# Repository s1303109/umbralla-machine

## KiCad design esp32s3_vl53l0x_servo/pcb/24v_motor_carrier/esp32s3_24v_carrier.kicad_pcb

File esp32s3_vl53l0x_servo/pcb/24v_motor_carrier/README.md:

# ESP32-S3／24V 馬達載板：KiCad 實作草稿

**狀態：DRAFT_NOT_FOR_FABRICATION。已實際建立原理圖、元件擺放、雙層銅箔、過孔與背面 GND 填充；未取得實物封裝與電氣驗證前，不可直接送製板。**

開啟 `esp32s3_24v_carrier.kicad_pro`。本專案附有本地符號庫、封裝庫及兩個 lib-table，不需要安裝全域元件庫。沒有操作遠端電腦上的 KiCad 視窗，也沒有修改原韌體或舊接線圖。

## 已完成

- 真正的 KiCad 8 `.kicad_sch`、`.kicad_pcb`、`.kicad_pro`，不是只有圖片。
- 23個封裝（含3個暫定固定孔）、33個功能網路；未使用 GPIO 另保留 KiCad 的單焊盤 NC 網路。
- 板外框包圍尺寸 **91.44 × 76.20 mm**，天線側有退讓切口；這是可檢查的第一版草稿，不宣稱最小尺寸或孔位已核准。
- 22個使用中的 GPIO 對照現有 `main/main.c` 與 `main/lcd_display.c`，GPIO1留空、GPIO35／36／37保留不接。
- R3 為 +5V_IN 到 K2_IN_L 的上拉；Q2 C 直接接 K2_IN_L。
- HC ECHO → R4 10kΩ → GPIO6分壓中點 → R5 20kΩ → GND。
- D1 有環端 K 接馬達切換正極、A 接GND；位於 K2 NO 後，與馬達並聯。
- 24V／馬達切換正極及直接回電源的馬達回流，用 **2.032mm** 預設銅線寬。此數字不構成任意銅厚、溫升、啟動電流下的容量保證。
- KiCad 8.0.9 原生 ERC／DRC、PCB與原理圖一致性檢查及網表逐端點比對。最後結果見 [reports/validation.json](reports/validation.json)。

## 如何看圖

- [原理圖 PDF](preview/schematic.pdf)
- [原理圖 PNG](preview/schematic.png)
- [完整雙層 PCB 預覽](preview/board_layers.png)
- [實際元件擺放與極性標示](preview/placement.png)
- [前面銅箔與絲印](preview/front.png)
- [背面銅箔](preview/back.png)
- [接頭腳位表 CSV](connector_pinout.csv)
- [全元件網路表 CSV](wiring_matrix.csv)
- [BOM／封裝狀態 CSV](bom.csv)

PCB上的 A1 是 ESP32 開發板插座。左側保留 USB 插拔方向，右側為天線退讓區；LCD以外接接頭J2表示，沒有將未確認的整片LCD孔位當成已核准製造尺寸。U5／U11等照片中的參考代號沒有直接沿用為本專案的實物焊盤代號。

擺放預覽依實際PCB封裝與焊盤座標重繪清楚標籤；原生F.Fab輸出另保留在 `preview/placement_native.svg`。銅箔與原理圖預覽均由KiCad原生輸出。

## 接頭與跳帽

**所有外接排針順序都是這份新載板定義的順序，不是宣稱與原LCD／模組原生排針完全相同。必須依下表和實物端子名稱製作接線，不能盲插。** 第1腳以方形焊盤標示。

| 元件 | 腳位順序 |
|---|---|
| J1 DC輸入，暫定5.08mm | 1＝外部+5V、2＝COM/GND、3＝+24V |
| JP1 外部5V連接 | 1＝+5V_IN、2＝+5V_ESP；使用外部5V時連接，USB供電前依原方案移除，不宣稱自動切換 |
| J2 LCD，1×16／2.54mm | 1 GND、2 +5V_ESP、3 RST、4 CS、5 RS、6 WR、7 RD、8 D0、9 D1、10 D2、11 D3、12 D4、13 D5、14 D6、15 D7、16 NC |
| J3 ToF1 | 1 VIN、2 GND、3 SCL、4 SDA、5 GPIO1/INT未接、6 XSHUT |
| J4 ToF2 | 1 VIN、2 GND、3 SCL、4 SDA |
| JP2／JP3 ToF供電 | 1 3V3、2 VIN、3 +5V_ESP；**預設不裝跳帽**，先確認模組VIN及I2C上拉電壓 |
| J5 HC-SR04 | 1 VCC、2 TRIG、3 ECHO、4 GND；ECHO經板上分壓後才到GPIO6 |
| J6 K1控制 | 1 DC+／+5V_IN、2 DC−／GND、3 IN／GPIO7；模組設H觸發 |
| J7 K2控制 | 1 VCC／+5V_ESP、2 GND、3 IN／K2_IN_L；由Q2拉低啟動 |
| J8 K2直流接點，暫定5.08mm | 1 → K2 COM（+24V）；2 ← K2 NO（切換正極）；NC不接 |
| J9 馬達，暫定5.08mm | 1 馬達＋、2 馬達－ |

J6只接K1控制側。**110V、L／N／PE與K1市電接點全部留在載板外**；本PCB沒有這些網路。

Q2封裝以 **E、B、C** 功能字母編號，使用暫定2.54mm引線成形／插接排列；它不是已確認的S9014、CS9013或2N3904通用腳序。E／B／C與D1 K／A已加在絲印，裝配前仍須核對實際零件。

## 製板前仍須完成

1. 實際 YD-ESP32-S3 V1.5 每腳、排距、排母、孔徑、USB與天線／機殼淨空確認。
2. 全部接頭的實際料號、腳距、線序、額定電流與線徑；LCD本體與排線接法。
3. ToF1／ToF2 供電與I2C上拉。JP2／JP3目前是開路選擇，未裝跳帽時感測器不會上電。
4. Q2實物型號、廠牌、腳序與封裝；K1輸入相容性、K2 IN電流與觸發門檻。
5. 24V電源啟動能力、馬達實際電流、K2直流馬達接點能力及D1續流／熱條件。
6. 銅厚、導線與端子的電流容量、過流保護、實際模組高度／固定孔及機構。

原D-50B照片為24V／1A，不能因布線完成就認定能啟動表列堵轉3A的馬達。程式仍含伺服測試服務；本PCB將GPIO1留空，未更動控制程式。

## 重產生與檢查

一般使用只需在 KiCad 8 或更新版本開啟 `.kicad_pro`。下列指令用於重建；需要KiCad 8的pcbnew Python綁定及CLI：

```sh
python3 scripts/build_project.py
python3 scripts/route_project.py
python3 scripts/finish_project.py
kicad-cli sch erc --format json --exit-code-violations -o reports/erc.json esp32s3_24v_carrier.kicad_sch
kicad-cli sch export netlist --format kicadxml -o reports/netlist.xml esp32s3_24v_carrier.kicad_sch
kicad-cli pcb drc --format json --schematic-parity --exit-code-violations -o reports/drc.json esp32s3_24v_carrier.kicad_pcb
python3 scripts/check_project.py
```

`build_project.py`會重新產生未完整布線的起始PCB；若要保留手動編輯，先另存副本再執行。腳本不讀寫韌體。

本機工具位於 `/opt/kicad8-validation`；環境設定已收在 `scripts/run_local.sh`。專案本身不依賴該絕對路徑即可在KiCad開啟。最初的檢查報告留在 `reports/history/`，正式結果以 `reports/erc.json`、`reports/drc.json`、`reports/validation.json`為準。

## 參考

- [Espressif：模組在載板上的天線擺放](https://docs.espressif.com/projects/esp-hardware-design-guidelines/en/latest/esp32s3/pcb-layout-design.html#general-principles-of-pcb-layout-for-modules-positioning-a-module-on-a-base-board)
- [Vishay 1N5408資料表](https://www.vishay.com/docs/88516/1n5400.pdf)：額定有熱條件，不能只看3A字樣。
- 本地原始庫來源、44腳對照、GPIO檔案SHA-256與待確認項目保留在 `design_contract.json`、`contract_review.md`。

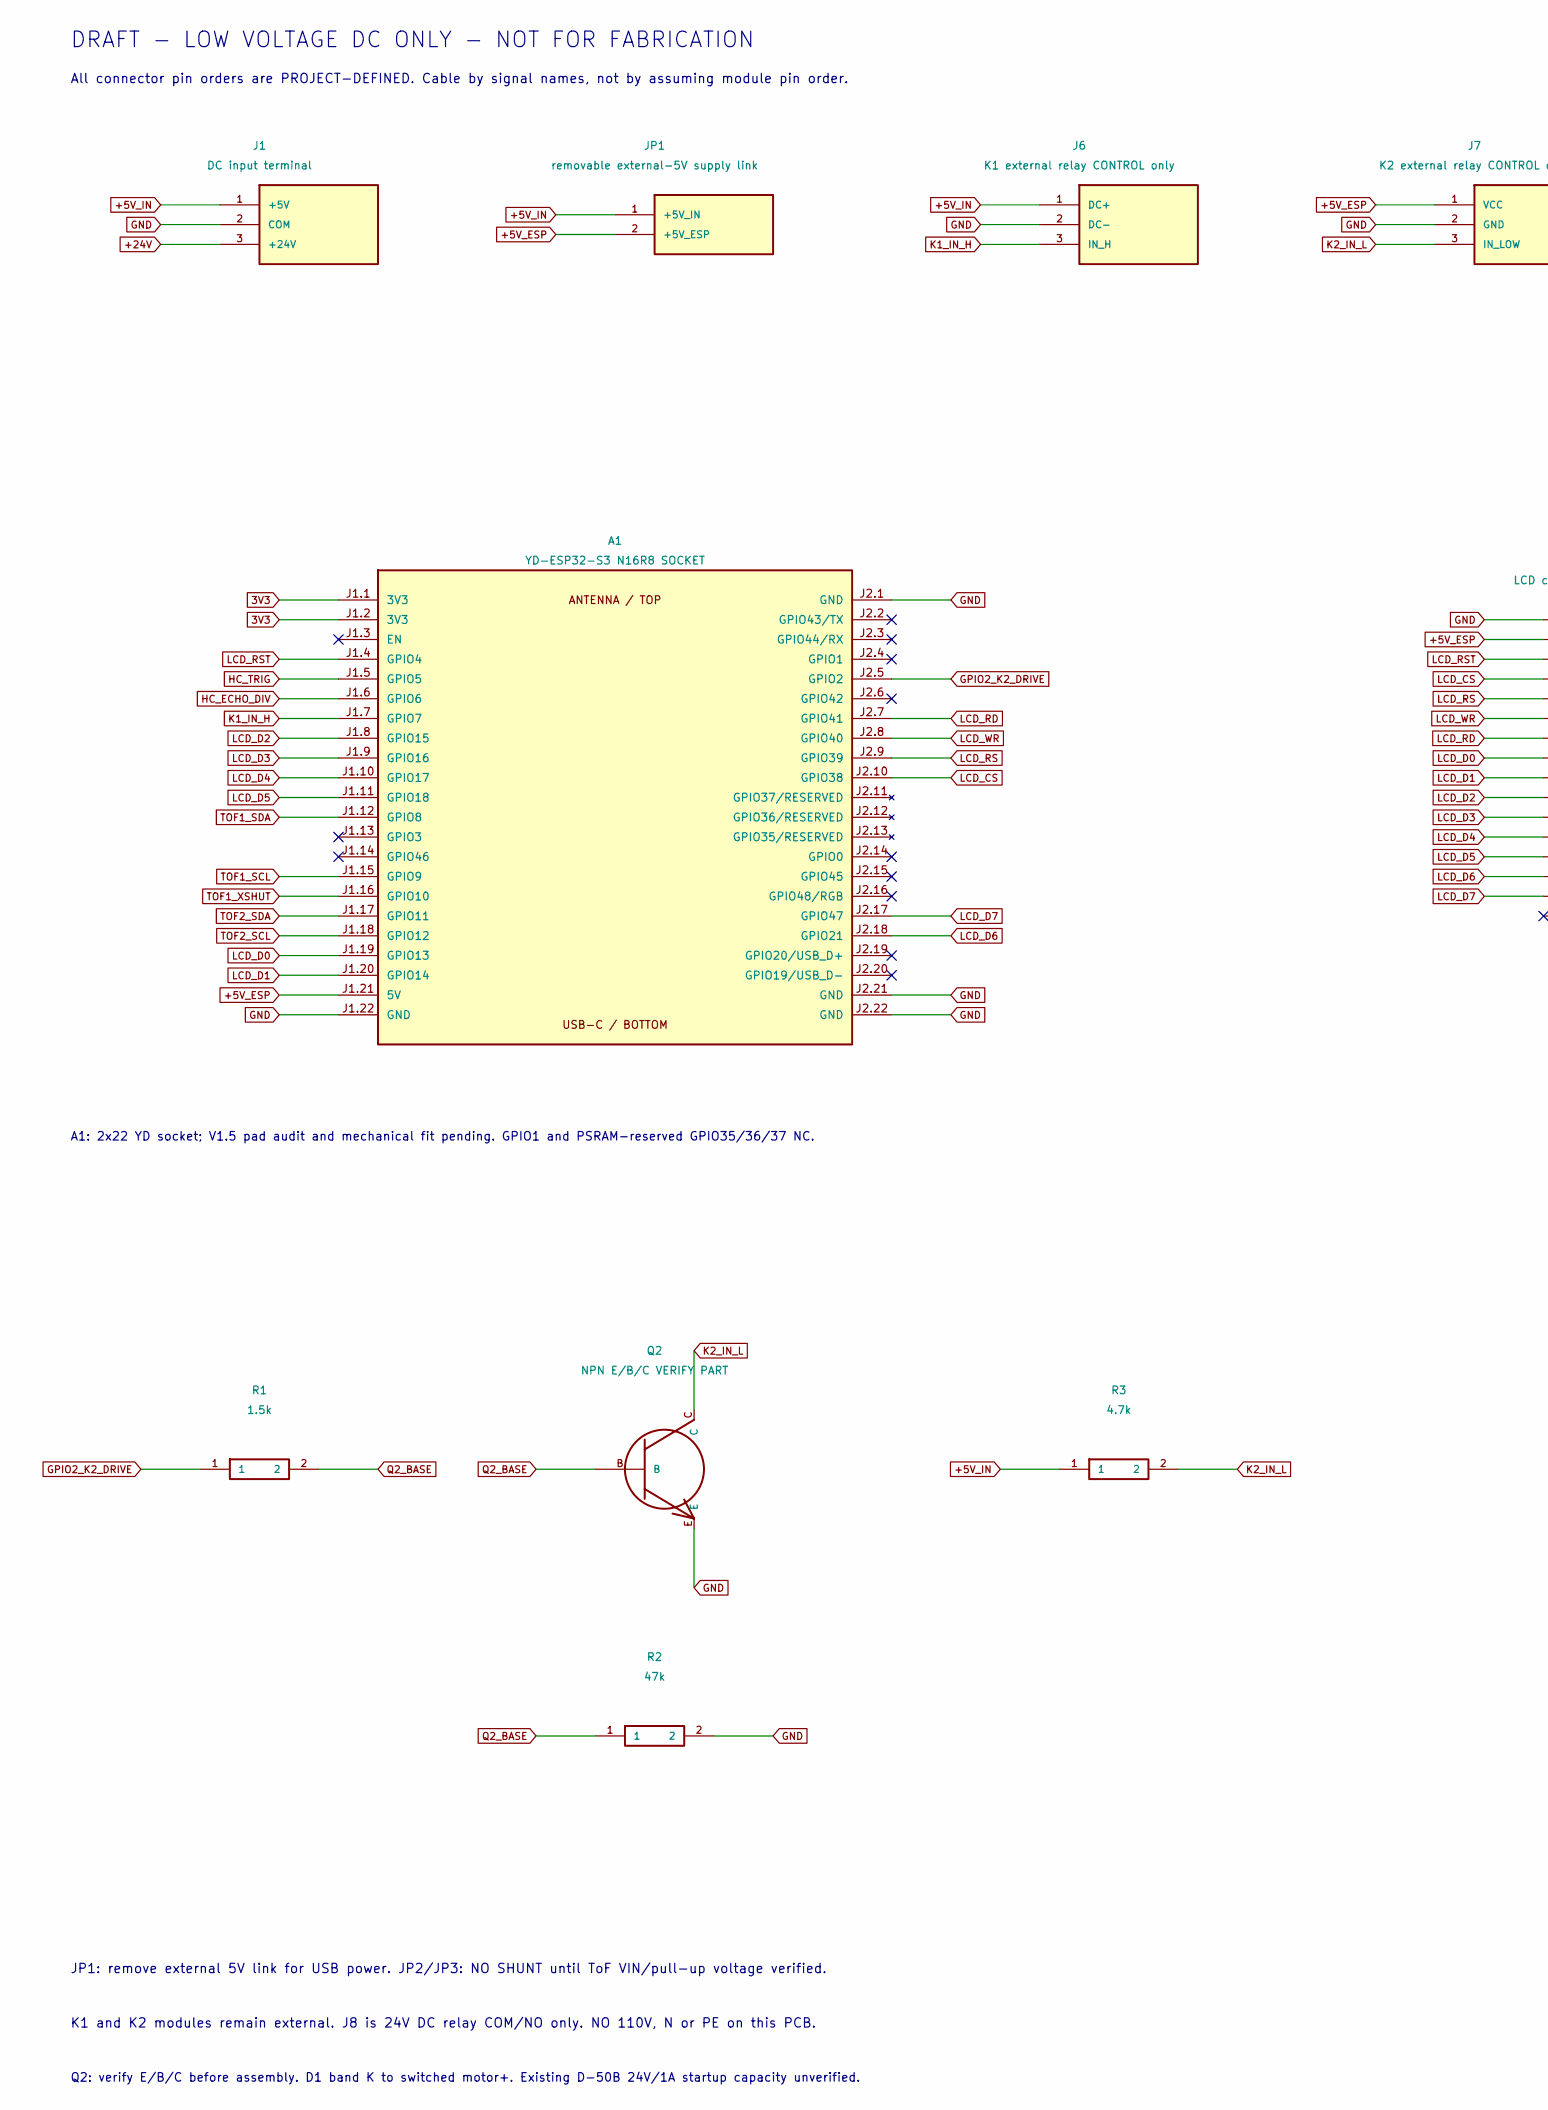
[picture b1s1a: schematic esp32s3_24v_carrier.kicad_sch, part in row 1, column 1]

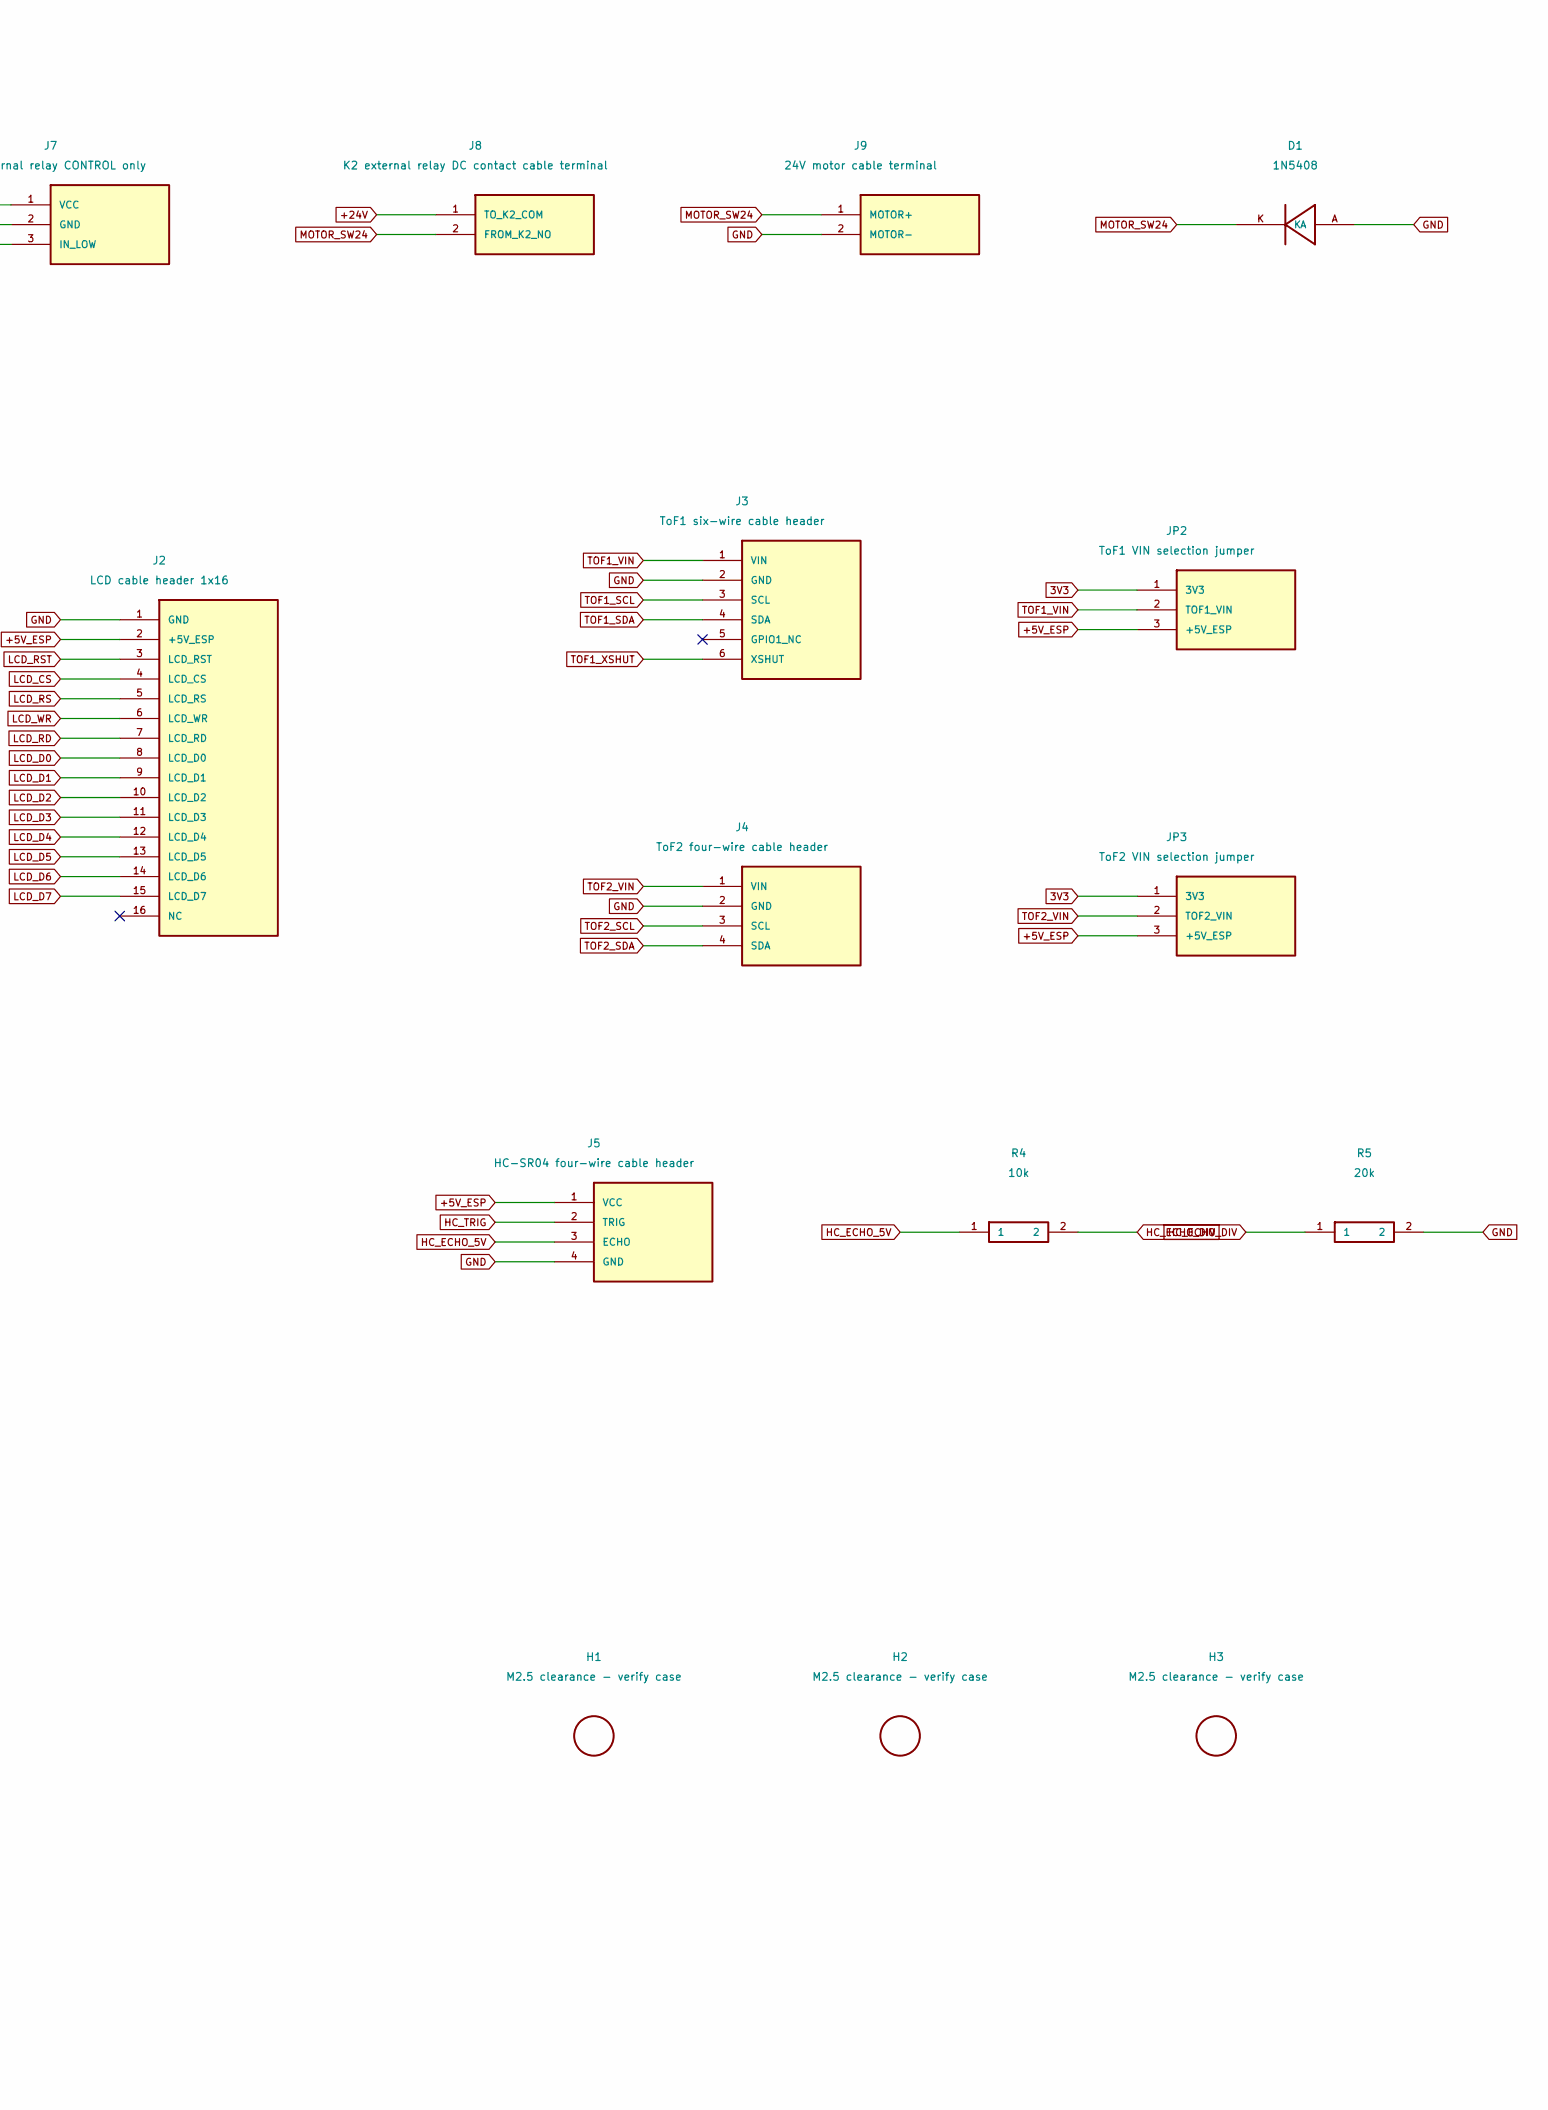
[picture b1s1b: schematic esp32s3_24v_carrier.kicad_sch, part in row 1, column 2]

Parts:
A1: YD-ESP32-S3 N16R8 SOCKET; YD-ESP32-S3_2x22_P2.54mm_Row25.40mm
D1: 1N5408; D_DO201_P15.24
H1, H2, H3: M2.5 clearance - verify case; MountingHole_2.7_GENERIC
J1: DC input terminal; Terminal_1x3_P5.08_GENERIC
J2: LCD cable header 1x16; Header_1x16_P2.54
J3: ToF1 six-wire cable header; Header_1x6_P2.54
J4: ToF2 four-wire cable header; Header_1x4_P2.54
J5: HC-SR04 four-wire cable header; Header_1x4_P2.54
J6: K1 external relay CONTROL only; Header_1x3_P2.54
J7: K2 external relay CONTROL only; Header_1x3_P2.54
J8: K2 external relay DC contact cable terminal; Terminal_1x2_P5.08_GENERIC
J9: 24V motor cable terminal; Terminal_1x2_P5.08_GENERIC
JP1: removable external-5V supply link; Header_1x2_P2.54
JP2: ToF1 VIN selection jumper; Header_1x3_P2.54
JP3: ToF2 VIN selection jumper; Header_1x3_P2.54
Q2: NPN E/B/C VERIFY PART; NPN_EBC_Wire_Form_VERIFY
R1: 1.5k; R_Axial_P7.62
R2: 47k; R_Axial_P7.62
R3: 4.7k; R_Axial_P7.62
R4: 10k; R_Axial_P7.62
R5: 20k; R_Axial_P7.62

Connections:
3V3: A1.J1.1 (3V3), A1.J1.2 (3V3), JP2.1 (3V3), JP3.1 (3V3)
+5V_ESP: A1.J1.21 (5V), J2.2 (+5V_ESP), J5.1 (VCC), J7.1 (VCC), JP1.2 (+5V_ESP), JP2.3 (+5V_ESP), JP3.3 (+5V_ESP)
+5V_IN: J1.1 (+5V), J6.1 (DC+), JP1.1 (+5V_IN), R3.1
+24V: J1.3 (+24V), J8.1 (TO_K2_COM)
GND: A1.J1.22 (GND), A1.J2.1 (GND), A1.J2.21 (GND), A1.J2.22 (GND), D1.A, J1.2 (COM), J2.1 (GND), J3.2 (GND), J4.2 (GND), J5.4 (GND), J6.2 (DC-), J7.2 (GND), J9.2 (MOTOR-), Q2.E, R2.2, R5.2
GPIO2_K2_DRIVE: A1.J2.5 (GPIO2), R1.1
HC_ECHO_5V: J5.3 (ECHO), R4.1
HC_ECHO_DIV: A1.J1.6 (GPIO6), R4.2, R5.1
HC_TRIG: A1.J1.5 (GPIO5), J5.2 (TRIG)
K1_IN_H: A1.J1.7 (GPIO7), J6.3 (IN_H)
K2_IN_L: J7.3 (IN_LOW), Q2.C, R3.2
LCD_CS: A1.J2.10 (GPIO38), J2.4 (LCD_CS)
LCD_D0: A1.J1.19 (GPIO13), J2.8 (LCD_D0)
LCD_D1: A1.J1.20 (GPIO14), J2.9 (LCD_D1)
LCD_D2: A1.J1.8 (GPIO15), J2.10 (LCD_D2)
LCD_D3: A1.J1.9 (GPIO16), J2.11 (LCD_D3)
LCD_D4: A1.J1.10 (GPIO17), J2.12 (LCD_D4)
LCD_D5: A1.J1.11 (GPIO18), J2.13 (LCD_D5)
LCD_D6: A1.J2.18 (GPIO21), J2.14 (LCD_D6)
LCD_D7: A1.J2.17 (GPIO47), J2.15 (LCD_D7)
LCD_RD: A1.J2.7 (GPIO41), J2.7 (LCD_RD)
LCD_RS: A1.J2.9 (GPIO39), J2.5 (LCD_RS)
LCD_RST: A1.J1.4 (GPIO4), J2.3 (LCD_RST)
LCD_WR: A1.J2.8 (GPIO40), J2.6 (LCD_WR)
MOTOR_SW24: D1.K, J8.2 (FROM_K2_NO), J9.1 (MOTOR+)
Q2_BASE: Q2.B, R1.2, R2.1
TOF1_SCL: A1.J1.15 (GPIO9), J3.3 (SCL)
TOF1_SDA: A1.J1.12 (GPIO8), J3.4 (SDA)
TOF1_VIN: J3.1 (VIN), JP2.2 (TOF1_VIN)
TOF1_XSHUT: A1.J1.16 (GPIO10), J3.6 (XSHUT)
TOF2_SCL: A1.J1.18 (GPIO12), J4.3 (SCL)
TOF2_SDA: A1.J1.17 (GPIO11), J4.4 (SDA)
TOF2_VIN: J4.1 (VIN), JP3.2 (TOF2_VIN)

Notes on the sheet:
DRAFT - LOW VOLTAGE DC ONLY - NOT FOR FABRICATION
All connector pin orders are PROJECT-DEFINED. Cable by signal names, not by assuming module pin order.
A1: 2x22 YD socket; V1.5 pad audit and mechanical fit pending. GPIO1 and PSRAM-reserved GPIO35/36/37 NC.
JP1: remove external 5V link for USB power. JP2/JP3: NO SHUNT until ToF VIN/pull-up voltage verified.
K1 and K2 modules remain external. J8 is 24V DC relay COM/NO only. NO 110V, N or PE on this PCB.
Q2: verify E/B/C before assembly. D1 band K to switched motor+. Existing D-50B 24V/1A startup capacity unverified.

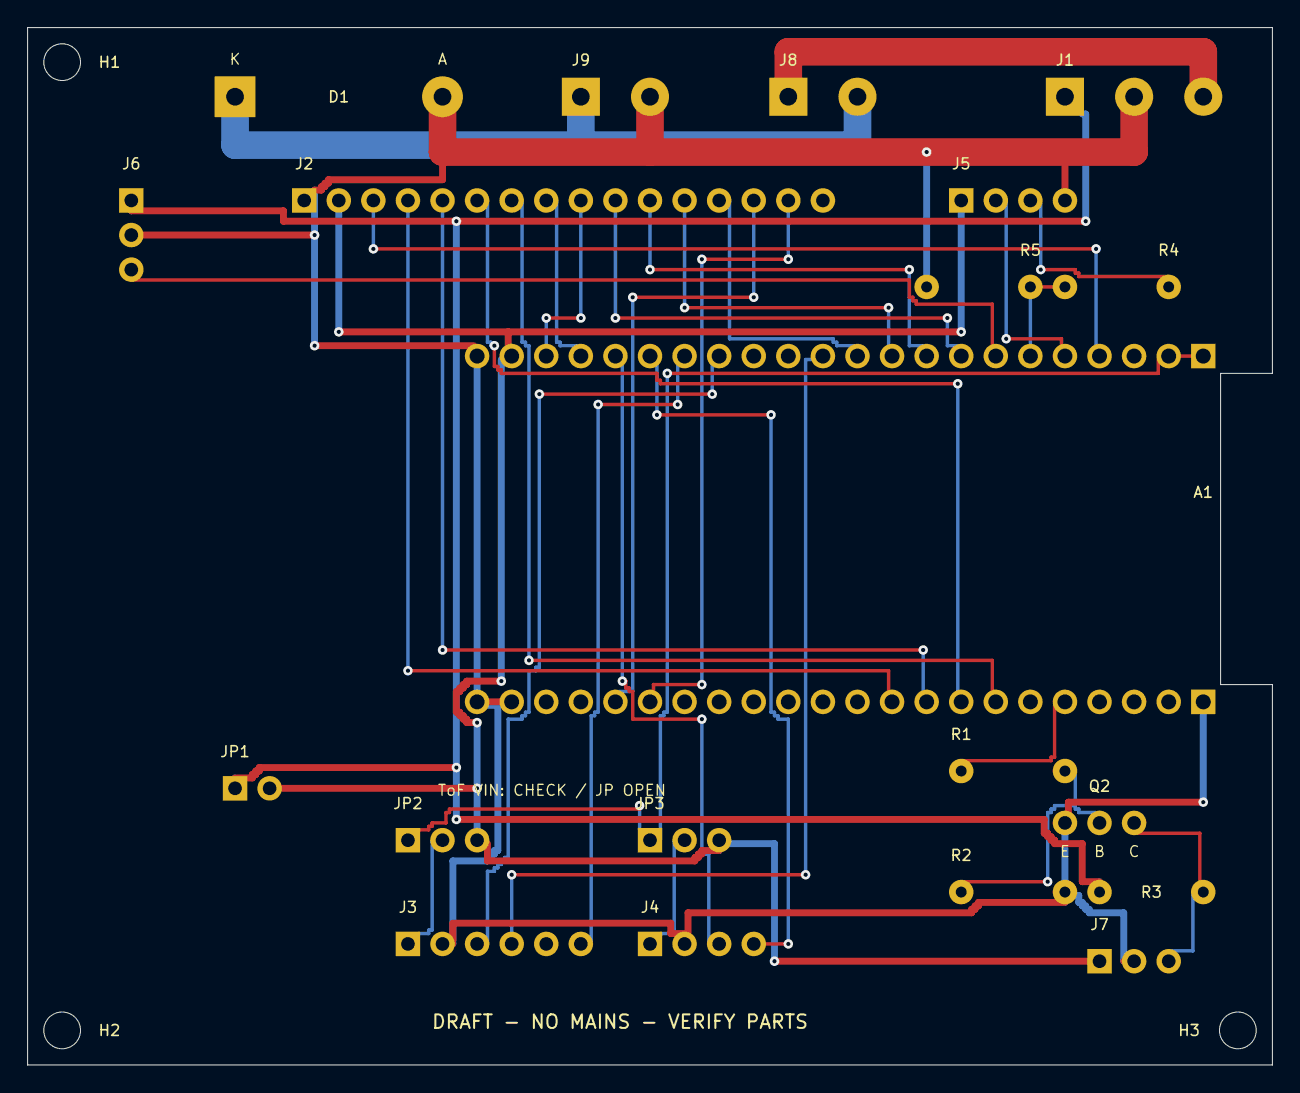
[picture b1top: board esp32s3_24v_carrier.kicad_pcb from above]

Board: 2 copper layers, 91.4 x 76.2 mm, 23 parts (0 on the bottom side), 33 nets.

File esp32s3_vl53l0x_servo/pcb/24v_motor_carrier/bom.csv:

Reference,Value,Kind,Footprint,Verification
A1,YD-ESP32-S3 N16R8 SOCKET,ESP32 development-board socket,CarrierDraft:YD-ESP32-S3_2x22_P2.54mm_Row25.40mm,V1.4 source mapping; V1.5 physical audit pending
J1,DC input terminal,DC input terminal,CarrierDraft:Terminal_1x3_P5.08_GENERIC,project-defined pin order; terminal model/current rating pending
JP1,removable external-5V supply link,removable external-5V supply link,CarrierDraft:Header_1x2_P2.54,remove before USB-powered operation; no automatic power ORing is claimed
J2,LCD cable header 1x16,LCD cable header 1x16,CarrierDraft:Header_1x16_P2.54,project-defined cable header; NOT native shield physical pin order; pin16 NC
J3,ToF1 six-wire cable header,ToF1 six-wire cable header,CarrierDraft:Header_1x6_P2.54,logical interface order only; actual connector/cable must be verified
J4,ToF2 four-wire cable header,ToF2 four-wire cable header,CarrierDraft:Header_1x4_P2.54,logical interface order only; no XSHUT control configured
JP2,ToF1 VIN selection jumper,ToF1 VIN selection jumper,CarrierDraft:Header_1x3_P2.54,VIN and I2C pull-up levels unverified; choose rail only after actual module check
JP3,ToF2 VIN selection jumper,ToF2 VIN selection jumper,CarrierDraft:Header_1x3_P2.54,VIN and I2C pull-up levels unverified; choose rail only after actual module check
J5,HC-SR04 four-wire cable header,HC-SR04 four-wire cable header,CarrierDraft:Header_1x4_P2.54,project-defined header; cable to actual silk labels
J6,K1 external relay CONTROL only,K1 external relay CONTROL only,CarrierDraft:Header_1x3_P2.54,no mains contact pads on carrier; actual relay module H trigger and 3.3V input compatibility pending
J7,K2 external relay CONTROL only,K2 external relay CONTROL only,CarrierDraft:Header_1x3_P2.54,actual IN sink current and VIH/VIL pending; intended Q2 collector total <=10mA
J8,K2 external relay DC contact cable terminal,K2 external relay DC contact cable terminal,CarrierDraft:Terminal_1x2_P5.08_GENERIC,24V DC only; external NC unused; terminal and relay motor-current ratings pending
J9,24V motor cable terminal,24V motor cable terminal,CarrierDraft:Terminal_1x2_P5.08_GENERIC,"JGB37-555 24V/7rpm listing: 0.14A no load,0.65A rated,3A stall; not measured"
Q2,NPN E/B/C VERIFY PART,NPN interface,CarrierDraft:NPN_EBC_Wire_Form_VERIFY,logical terminals only; vendor-specific physical pad order MUST be confirmed; generic footprint is candidate only
R1,1.5k,resistor,CarrierDraft:R_Axial_P7.62,Generic candidate; verify hardware/mechanics
R2,47k,resistor,CarrierDraft:R_Axial_P7.62,Generic candidate; verify hardware/mechanics
R3,4.7k,resistor,CarrierDraft:R_Axial_P7.62,Generic candidate; verify hardware/mechanics
R4,10k,resistor,CarrierDraft:R_Axial_P7.62,Generic candidate; verify hardware/mechanics
R5,20k,resistor,CarrierDraft:R_Axial_P7.62,Generic candidate; verify hardware/mechanics
D1,1N5408,flyback diode candidate,CarrierDraft:D_DO201_P15.24,band K to switched motor+; pulse/thermal validation pending; 3A average rectifier rating does not alone prove suitability
H1,M2.5 clearance - verify case,mount,CarrierDraft:MountingHole_2.7_GENERIC,Generic candidate; verify hardware/mechanics
H2,M2.5 clearance - verify case,mount,CarrierDraft:MountingHole_2.7_GENERIC,Generic candidate; verify hardware/mechanics
H3,M2.5 clearance - verify case,mount,CarrierDraft:MountingHole_2.7_GENERIC,Generic candidate; verify hardware/mechanics

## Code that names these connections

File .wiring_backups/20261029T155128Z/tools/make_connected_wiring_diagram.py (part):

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    data = [int(v) for v in re.findall(r'GPIO_NUM_(\d+)', data[1])]
    assert len(data) == 8
    expected = {'SERVO_SIGNAL_PIN': 1, 'MOTOR_RELAY_PIN': 2, 'RELAY_PIN': 7,
                'LCD_RST_PIN': 4, 'HC_SR04_TRIG_PIN': 5, 'HC_SR04_ECHO_PIN': 6}
    for key, value in expected.items():
        assert pinmap[key] == value, f'Review diagram layout after changing {key}'
    return pinmap, data
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def main():
    pins, data = get_pins()
    text(60, 60, '目前接線連接圖｜沿每條線看起點與終點', 43, INK, True)
    text(60, 105, '伺服測試版：GPIO1＝伺服訊號；GPIO2＝Q2／K2；GPIO7＝K1；GPIO4＝LCD RESET。', 27)
    text(60, 147, '同名 G／+5V BUS／+5V_F4 是同一電氣節點；有圓點才表示分支相接。框內接點不是實物腳位排列。', 24, GRAY)
    line([(65, 181), (130, 181)], BLUE); text(145, 189, '訊號', 22)
    line([(310, 181), (375, 181)], RED); text(390, 189, '正電源', 22)
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    text(95, 460, 'ESP32：USB 與外部 5V', 24, INK, True)
    text(95, 493, '沿用原 EXT-5V 隔開方式。', 23)
    text(95, 550, 'LCD／ToF 的實際供電待確認，沒有擅自接到這條 5V 母線。', 23, AMBER, True)
    text(95,588,'ESP32 GPIO7',25,INK,True)
    wire('S14','ESP32 GPIO7','K1 IN',[(360,580),(1150,580)],'K1_IN',GREEN,label=(840,568))
    text(1180,588,'K1 IN；H 觸發，原 DC／JD 供電跳帽保持連接',24,GREEN,True)
    line([(115, 620), (2290, 620)], INK, 6)
    text(2303,629,'G',24,INK,True)
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    ground(1370,1290,'同 A 區 G')

    # C: one complete base/collector/emitter circuit, not a parts list.
    panel(1365,610,'C｜GPIO2、R1／R2／R3、Q2 與 K2 IN 的完整接點','Q2 只拉低 K2 IN，不直接承受伺服電流。S9014 實體腳序未核實；圖中只標 B／C／E。','#f6f3ff')
    nodebox(95,1480,390,90,'A 區 F4 後 +5V_F4','同一節點供 K2 VCC 與 R3')
    nodebox(1810,1480,460,90,'K2 VCC','固定 5V，不接 6V／24V')
    wire('P12','F4 輸出 +5V_F4','K2 VCC',[(485,1525),(1810,1525)],'+5V_F4',RED,label=(800,1512))
    dot(1520,1525,RED)
    wire('R3a','+5V_F4','R3 4.7kΩ 上端',[(1520,1525),(1520,1565)],'+5V_F4',RED)
    resistor(1520,1565,1520,1640,'R3 4.7kΩ',RED)
    nodebox(95,1660,275,90,'ESP32 GPIO2','HIGH＝啟動 K2')
    wire('S02','ESP32 GPIO2','R1 1.5kΩ 一端',[(370,1705),(470,1705)],'K2_DRIVE',VIOLET)
    resistor(470,1705,610,1705,'R1 1.5kΩ',VIOLET)
    wire('R1b','R1 1.5kΩ 另一端','Q2 B／R2 上端',[(610,1705),(900,1705)],'Q2_BASE',VIOLET,label=(640,1690))
    dot(730,1705,VIOLET)
    wire('R2a','Q2 B 節點','R2 47kΩ 上端',[(730,1705),(730,1790)],'Q2_BASE',VIOLET)
    resistor(730,1790,730,1860,'R2 47kΩ',VIOLET)
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    text(2240,2343,'VIN',18,AMBER,True,'end')
    text(1640,2250,'GND 都已接到 A 區 G；中斷腳未使用。',21,GRAY)
    text(1640,2280,'ToF2 XSHUT 的現有使能方式待核實。',21,AMBER)
    nodebox(95,2460,470,80,'ESP32 GPIO5')
    box(1760,2470,500,175);text(2010,2505,'HC-SR04',27,INK,True,'middle')
    wire('S09','ESP32 GPIO5','HC-SR04 TRIG',[(565,2500),(1760,2500)],'HC_TRIG',GREEN,label=(770,2488));text(1780,2532,'TRIG',23,GREEN,True)
    nodebox(95,2550,470,80,'ESP32 GPIO6')
    text(1780,2583,'ECHO',23,BLUE,True)
    wire('S10','HC-SR04 ECHO','10kΩ 分壓上臂',[(1760,2575),(1440,2575)],'HC_ECHO_5V',BLUE)
    resistor(1280,2575,1440,2575,'10kΩ',BLUE)
    wire('S11','10kΩ 另一端／20kΩ 上端','ESP32 GPIO6',[(1280,2575),(1000,2575),(1000,2590),(565,2590)],'HC_ECHO_DIV',BLUE,label=(660,2576))
    dot(1000,2575,BLUE)
    wire('S12','GPIO6 分壓節點','20kΩ 一端',[(1000,2575),(1000,2630),(1090,2630)],'HC_ECHO_DIV',BLUE)
    resistor(1090,2630,1250,2630,'20kΩ',BLUE)
    wire('S13','20kΩ 另一端','G 共地排',[(1250,2630),(1410,2630)],'G',INK)
    ground(1410,2630,'同 A 區 G')
    text(1780,2620,'VCC → A 區 5V；GND → A 區 G',21,GRAY)

    # E: thirteen direct parallel traces with both endpoints labelled.
    panel(2695,740,'E｜LCD 完整平行訊號：沿同一條橫線接，不按排針序號猜測','GPIO4 是 LCD RESET；LCD_D0～D7 的順序不能交換。SD 卡端子目前程式未配置。','#f4f9ff')
    box(95,2805,475,570);box(1670,2805,590,570)
    text(330,2845,'ESP32',28,INK,True,'middle');text(1965,2845,'3.5 吋 LCD Shield',28,INK,True,'middle')
    lcd=[(pins[k],name) for k,name in [('LCD_RST_PIN','LCD_RST'),('LCD_CS_PIN','LCD_CS'),('LCD_RS_PIN','LCD_RS'),('LCD_WR_PIN','LCD_WR'),('LCD_RD_PIN','LCD_RD')]]
    lcd += [(gpio,f'LCD_D{i}') for i,gpio in enumerate(data)]
    for i,(gpio,name) in enumerate(lcd):
        y=2880+i*38;color=GREEN if i<5 else BLUE;wid=f'L{i+1:02}'
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
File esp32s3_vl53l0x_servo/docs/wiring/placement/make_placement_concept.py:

"""Concept placement only: no KiCad netlist, pad geometry, or fabrication data."""
from pathlib import Path
from html import escape
OUT = Path(__file__).resolve().parent
S = []

def text(x,y,value,size=22,bold=False,color='#17324d'):
    S.append(f'<text x="{x}" y="{y}" font-size="{size}" font-weight="{700 if bold else 400}" fill="{color}">{escape(value)}</text>')

def box(x,y,w,h,fill='#fff',stroke='#54758c',dash=False,r=10):
    S.append(f'<rect x="{x}" y="{y}" width="{w}" height="{h}" rx="{r}" fill="{fill}" stroke="{stroke}" stroke-width="2"'+(' stroke-dasharray="10 7"' if dash else '')+'/>')

def path(d,color='#2584c5',width=3,dash=False,arrow=False):
    S.append(f'<path d="{d}" fill="none" stroke="{color}" stroke-width="{width}"'+(' stroke-dasharray="8 6"' if dash else '')+(' marker-end="url(#arrow)"' if arrow else '')+'/>')

def pads(x,y,count,step=28):
    for i in range(count):
        S.append(f'<circle cx="{x+step*i}" cy="{y}" r="6" fill="#e4af38" stroke="#8a691a" stroke-width="2"/>')

text(60,58,'PCB 元件擺放建議｜依第一張零件、第二張接線功能',34,True)
text(60,99,'相對位置示意，不按比例；未取得原始 PCB、完整模組外形與固定孔，不能作製板尺寸或銅箔圖。',20,color='#a64819')
text(60,148,'A. LCD 與 ESP32 維持同面：先把 ESP32 橫放在 LCD 下方',28,True)
box(80,195,1000,1120,'#f0f8f4','#3d8b6f',True)
text(105,229,'載板區域示意（外形最後再定，不是正式 Edge.Cuts）',21,True)
# The real display outline determines the upper part of a direct-mounted board.
box(140,270,880,440,'#e7edf5','#536b88')
text(350,355,'U11：3.5 吋 LCD',32,True)
text(320,407,'先固定實際位置、方向、孔位',25)
text(302,449,'若線材外接，載板只需保留對應插座',22,color='#9d5520')
pads(420,291,10,29); pads(420,688,10,29)
text(170,659,'資料腳排朝向 ESP32；實際腳序按網表核對',21,True)
# A horizontal development-board body, with antenna edge and plug corridor.
box(65,790,650,190,'#edf0ff','#7165a5')
box(65,790,108,190,'#f4ddf9','#a65aaf',True)
text(80,835,'天線',24,True,color='#8e3d96')
text(80,872,'朝板外',20,color='#8e3d96')
path('M80 922 H22','#a65aaf',3,arrow=True)
text(250,865,'U5：ESP32-S3 橫放',27,True)
text(205,909,'含 GPIO13～18 的排針朝向 LCD',22,True)
text(205,947,'依飛線選轉向，不預設 R90／R270',20)
pads(205,808,22,23); pads(205,962,22,23)
box(715,843,345,91,'#fff8df','#cb9a33',True)
text(735,880,'USB 插頭／拔插通道',22,True)
text(735,914,'此區不擺接頭或高零件',19)
for i in range(5):
    path(f'M{455+i*27} 710 L{420+i*27} 790','#2584c5',2,True)
text(410,755,'優先布 LCD 資料與控制線',20,True)
# Functional local groups rather than a row of unrelated resistors.
box(130,1035,175,80,'#e6f8ff','#3096ae')
text(145,1066,'HC-SR04 接頭',20,True)
text(145,1098,'靠 GPIO5／6 側',18)
box(330,1028,205,90,'#fff2de','#c18c35')
text(345,1063,'R4 10k／R5 20k',20,True)
text(345,1096,'靠 GPIO6 分壓中點',18)
box(580,1020,180,115,'#fff2de','#c18c35')
text(595,1053,'Q2＋R1／R2',20,True)
text(595,1083,'R3 靠 IN／C',19)
text(595,1113,'靠 GPIO2 側',18)
box(800,1010,240,100,'#ffecdf','#c97736')
text(815,1044,'U4／K2 馬達支路',21,True)
text(815,1077,'接點朝電源／馬達端',18)
box(130,1185,175,80,'#e6f8ff','#3096ae')
text(145,1217,'K1 控制接口',20,True)
text(145,1246,'5V／GND／IN7',18)
box(330,1185,180,80,'#e6f8ff','#3096ae')
text(345,1218,'ToF1 接頭',21,True)
text(345,1247,'靠 GPIO8／9／10',17)
box(535,1185,185,80,'#e6f8ff','#3096ae')
text(550,1218,'ToF2 接頭',21,True)
text(550,1247,'靠 GPIO11／12',18)
box(850,1140,190,57,'#ffe4df','#be573e')
text(865,1176,'DC 電源入口',21,True)
box(850,1220,190,57,'#ffe4df','#be573e')
text(865,1256,'U7 馬達接口',21,True)
box(755,1217,78,64,'#fff2de','#c18c35')
text(767,1256,'D1',23,True)
path('M945 1197 V1220','#be573e',3,True)
text(1115,227,'擺放時保留的限制',25,True)
box(1110,250,340,1065,'#fff','#b8c5d2')
notes=[
('LCD 大外框不能任意縮小', '直插才需要預留整塊模組；', '外接時改用已確認的接頭。'),
('ESP32 天線及 USB 要留空', '天線避開 LCD 金屬背板；', 'USB 線要能插入與拔出。'),
('電阻按功能分組', 'R1／R2 靠 Q2；R3 靠 IN。', 'R4／R5 靠 GPIO6。'),
('馬達支路靠板邊', '電源、K2、D1、輸出靠近；', '回流直接回電源入口。'),
('U1／U2 的市電側另置', '此圖載板只放 DC 與控制口；', 'AC 接線功能仍依第二張圖。'),
('虛線不代表實際銅箔', '沒有指定焊盤座標或走線；', '不能由這張圖產生 Gerber。')]
for i,(head,a,b) in enumerate(notes):
    y=298+i*165
    text(1130,y,head,21,True)
    text(1130,y+37,a,18)
    text(1130,y+69,b,18)
text(85,1362,'實際封裝若為整塊繼電器模組，須以模組本體外形取代小接頭圖框；同面零件不可因只看焊盤而互相重疊。',19,color='#a64819')
text(60,1430,'B. 機構允許時更省面積：LCD 在正面，ESP32 與小零件在背面',28,True)
box(80,1460,1370,285,'#f7f5fe','#8b78ac')
box(140,1512,620,65,'#e7edf5','#536b88')
text(312,1555,'LCD／金屬背板',25,True)
path('M205 1577 V1620 M690 1577 V1620','#54758c',8)
box(160,1620,580,36,'#edf0ff','#7165a5',r=3)
text(240,1696,'背面 ESP32／載板；高度與孔位必須核對',21,True)
text(820,1518,'這是省平面面積的候選方案，',22,True)
text(820,1561,'不是把兩個同面封裝直接重疊。',21)
text(820,1604,'天線須避開 LCD 金屬投影與 RF 淨空區；',20)
text(820,1647,'需保留插座高度、螺絲、絕緣與 USB 空間。',20)
text(60,1800,'布線保持第二張圖與程式的 GPIO 對應；先修正原理圖／網表，再做 ERC、佈局、DRC。',21,True)
text(60,1840,'若 LCD、繼電器及感測器均線材外接，最省面積的載板只需 ESP32 插座、小零件與板邊接頭。',20,color='#276c53')
svg='<svg xmlns="http://www.w3.org/2000/svg" width="1500" height="1880" viewBox="0 0 1500 1880"><defs><marker id="arrow" markerWidth="8" markerHeight="8" refX="7" refY="4" orient="auto"><path d="M0 0 L8 4 L0 8 Z" fill="#a65aaf"/></marker></defs><style>text{font-family:"Noto Sans CJK TC",sans-serif}</style><rect width="1500" height="1880" fill="#fafcfe"/>'+''.join(S)+'</svg>'
(OUT/'pcb_placement_concept.svg').write_text(svg,encoding='utf-8')
print(OUT/'pcb_placement_concept.svg')
